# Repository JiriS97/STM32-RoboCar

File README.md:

# STM32-RoboCar
All of this work is licensed under the MIT License - please see license.txt for details.

STM32 based robotic car

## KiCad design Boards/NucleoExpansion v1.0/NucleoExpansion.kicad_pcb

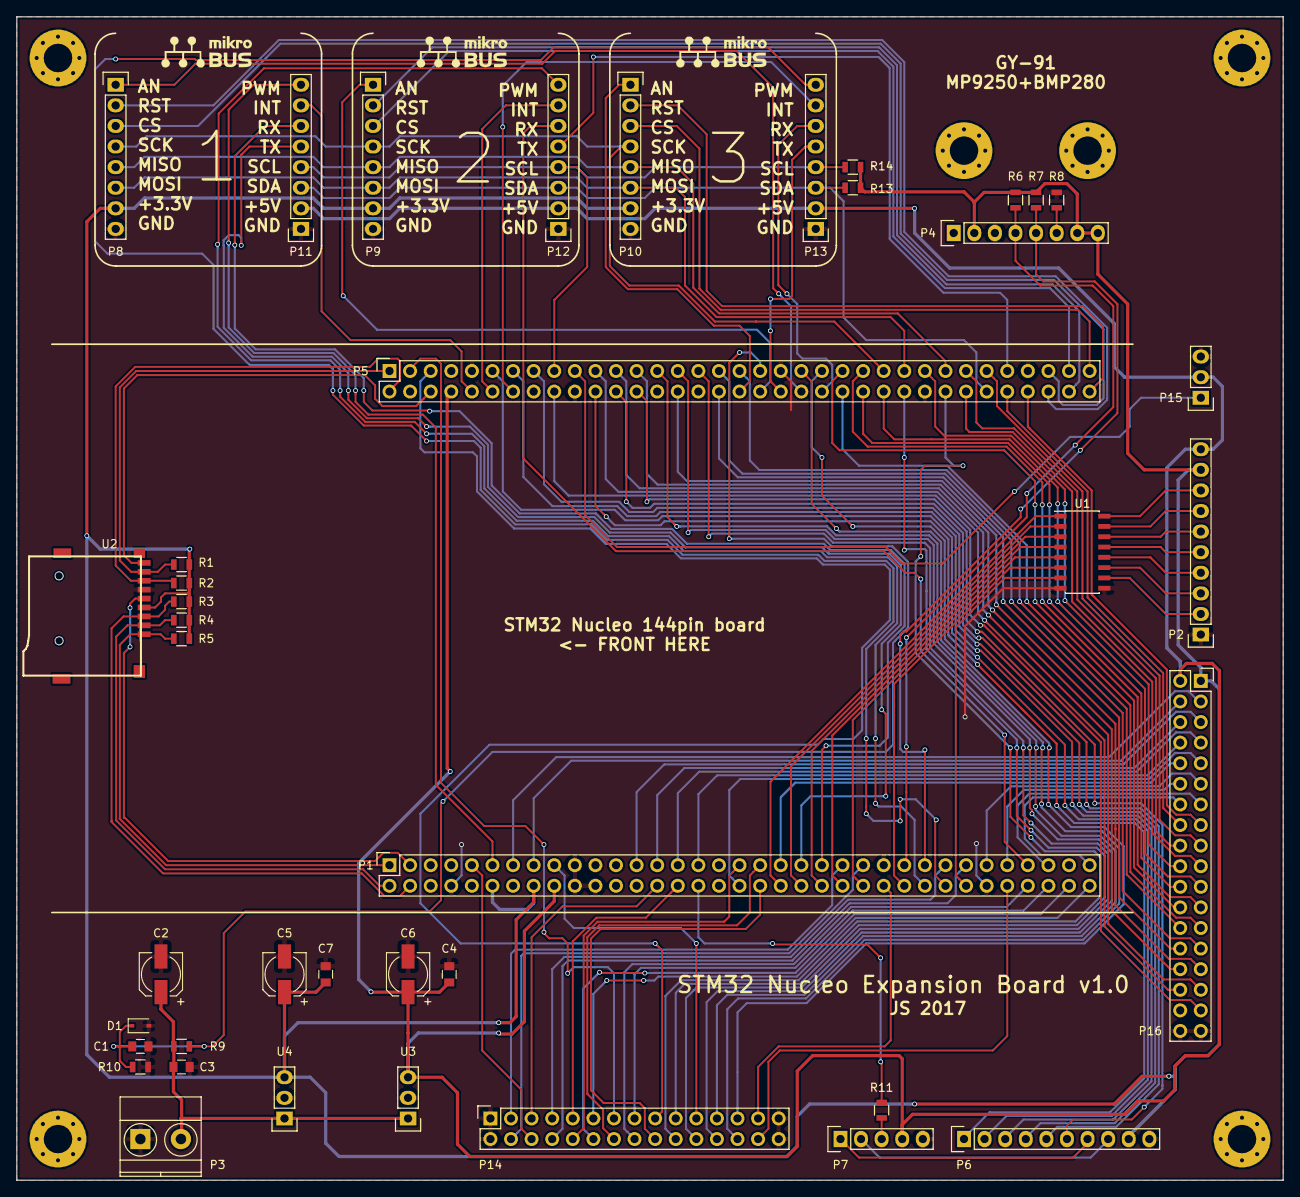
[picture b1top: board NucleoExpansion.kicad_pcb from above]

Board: 2 copper layers, 156.2 x 143.5 mm, 41 parts (0 on the bottom side), 123 nets.

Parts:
C1, C3, C6, C7: 100n; C_0805
C2, C4, C5: 10u; CP_Elec_5x5.7
D1: 3V3; D_SOD-323
P1, P5: CONN_02X35; Socket_Strip_Straight_2x35
P2: TRANSISTOR_OUT; Socket_Strip_Straight_1x10
P3: POWER_IN; TerminalBlock_Pheonix_MKDS1.5-2pol
P4: 10-DOF; Socket_Strip_Straight_1x08
P6: LCD; Socket_Strip_Straight_1x10
P7: AUDIO/ANALOG; Socket_Strip_Straight_1x05
P8: MIKROBUS1.L; Socket_Strip_Straight_1x08
P9: MIKROBUS2.L; Socket_Strip_Straight_1x08
P10: MIKROBUS3.L; Socket_Strip_Straight_1x08
P11: MIKROBUS1.R; Socket_Strip_Straight_1x08
P12: MIKROBUS2.R; Socket_Strip_Straight_1x08
P13: MIKROBUS3.R; Socket_Strip_Straight_1x08
P14: MOTOR; Socket_Strip_Straight_2x15
P15: LED; Socket_Strip_Straight_1x03
P16: FREE_PINS; Socket_Strip_Straight_2x18
R1, R2: 47K; R_0805
R3, R4, R5: 47k; R_0805
R6, R7, R13, R14: 4k7; R_0805
R8: 100R; R_0805
R9: 9k1; R_0805
R10: 1k; R_0805
R11: 10R; R_0805
U1: ULN2003; SOIC-16_3.9x9.9mm_Pitch1.27mm
U2: MicroSD_SPI_CD; microsd
U3: K7805; Socket_Strip_Straight_1x03
U4: K7803; Socket_Strip_Straight_1x03

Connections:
+3V3: C5.1, C7.1, P1.12, P1.16, P2.9, P4.2, P4.7, P4.8, P6.9, P8.7, P9.7, P10.7, P16.1, R1.1, R2.1, R3.1, R4.1, R5.1, R6.1, R7.1, R13.1, R14.1, U2.4, U4.3
+5V: C4.1, C6.1, P1.18, P2.10, P5.8, P7.4, P11.2, P12.2, P13.2, P15.2, P16.2, U3.3
/FREE1: P1.13, P16.3
/FREE2: P1.15, P16.4
/FREE3: P1.25, P16.5
/FREE4: P1.27, P16.6
/FREE5: P1.29, P16.7
/FREE6: P1.31, P16.8
/FREE7: P1.36, P16.9
/FREE8: P1.39, P16.10
/FREE9: P1.59, P16.11
/FREE10: P1.61, P16.12
/FREE11: P1.65, P16.13
/FREE12: P1.69, P16.14
/FREE13: P5.64, P16.15
/FREE14: P5.62, P16.16
/FREE15: P5.59, P16.17
/FREE16: P5.57, P16.18
/FREE17: P5.58, P16.19
/FREE18: P5.53, P16.20
/FREE19: P5.50, P16.21
/FREE20: P5.48, P16.22
/FREE21: P5.47, P16.23
/FREE22: P5.45, P16.24
/FREE23: P5.46, P16.25
/FREE24: P5.35, P16.26
/FREE25: P5.33, P16.27
/FREE26: P5.34, P16.28
/FREE27: P5.30, P16.29
/FREE28: P5.25, P16.30
/FREE29: P5.23, P16.31
/FREE30: P5.21, P16.32
/FREE31: P5.18, P16.33
/LCD.AUDIO+: P6.7, P7.1
/LCD.AUDIO-: P6.8, P7.2
/PA0/PWM5.1/MOTOR1.EN: P1.28, P14.5
/PA1/PWM5.2/MOTOR2.EN: P1.30, P14.9
/PA3/AN3/BATTERY_AN: C1.1, D1.1, P5.37, R9.2, R10.1
/PA4/ANALOG_OUT: P1.32, R11.2
/PA5/SPI1.SCK/LCD.SCK: P5.11, P6.2
/PA6/SPI1.MISO/LCD.MISO: P5.13, P6.3
/PA7/SPI.MOSI/LCD.MOSI: P5.15, P6.4
/PA11/CLICK3.INT: P5.14, P13.7
/PA12/CLICK2.INT: P5.12, P12.7
/PA15/PWM2.1/ENC2.1: P1.17, P14.21
/PB1/LCD.INT: P5.24, P6.5
/PB2/LCD.CS: P5.22, P6.1
/PB3/PWM2.2/ENC2.2: P5.31, P14.22
/PB4/PWM3.1/ENC3.1: P5.27, P14.23
/PB5/PWM3.2/ENC3.2: P5.29, P14.24
/PB6/I2C4.SCL/CLICK.SCL: P5.17, P11.4, P12.4, P13.4, R14.2
/PB8/PWM10.1/MOTOR3.EN: P5.3, P14.13
/PB9/PWM11.1/MOTOR4.EN: P5.5, P14.17
/PB15/LCD.PD: P5.26, P6.6
/PC0/ADC123.IN10/MOTOR4.AN: P1.38, P14.18
/PC2/ADC123.IN12/MOTOR2.AN: P1.35, P14.10
/PC3/ADC123.IN13/MOTOR3.AN: P1.37, P14.14
/PC5/SDMMC.DETECT: P5.6, U2.9
/PC7/PWM8.2/NEOPIXEL: P5.19, P15.1
/PC8/SDMMC.D0: P5.2, R2.2, U2.7
/PC9/SDMMC.D1: P5.1, R1.2, U2.8
/PC10/SDMMC.D2: P1.1, R5.2, U2.1
/PC11/SDMMC.D3: P1.2, R4.2, U2.2
/PC12/SDMMC.CK: P1.3, U2.5
/PD0/MOTOR2.B: P1.57, P14.8
/PD1/MOTOR2.A: P1.55, P14.7
/PD2/SDMMC.CMD: P1.4, R3.2, U2.3
/PD3/TRANSISTOR.1: P1.40, U1.1
/PD5/USART2.TX/CLICK1.TX: P1.41, P11.5
/PD6/USART2.RX/CLICK1.RX: P1.43, P11.6
/PD7/MOTOR1.A: P1.45, P14.3
/PD8/CLICK1.INT: P5.10, P11.7
/PD10/CLICK1.CS: P5.65, P8.3
/PD12/PWM4.1/ENC4.1: P5.43, P14.25
/PD13/PWM4.2/ENC4.2: P5.41, P14.26
/PE2/TRANSISTOR.4: P1.46, U1.4
/PE3/MOTOR1.B: P1.47, P14.4
/PE4/TRANSISTOR.5: P1.48, U1.5
/PE5/PWM9.1/SERVO1: P1.50, P14.27
/PE6/PWM9.2/SERVO2: P1.62, P14.28
/PE7/USART7.RX/CLICK3.RX: P5.44, P13.6
/PE8/USART7.TX/CLICK3.TX: P5.40, P13.5
/PE9/PWM1.1/ENC1.1: P5.52, P14.19
/PE11/PWM1.2/ENC1.2: P5.56, P14.20
/PE12/SPI4.SCK: P5.49, P8.4, P9.4, P10.4
/PE13/SPI4.MISO: P5.55, P8.5, P9.5, P10.5
/PE14/SPI4.MOSI: P5.51, P8.6, P9.6, P10.6
/PF0/I2C2.SDA: P1.53, P4.5, R7.2
/PF1/I2C2.SCL: P1.51, P4.4, R6.2
/PF2/TRANSISTOR.6: P1.52, U1.6
/PF4/ADC3.IN14/CLICK2.AN: P5.38, P9.1
/PF5/ADC3.IN15/CLICK3.AN: P5.36, P10.1
/PF6/ADC3.IN4/MOTOR1.AN: P1.9, P14.6
/PF7/PWM11.1/CLICK1.PWM: P1.11, P11.8
/PF8/PWM13.1/CLICK2.PWM: P1.54, P12.8
/PF9/PWM14.1/CLICK3.PWM: P1.56, P13.8
/PF10/ADC3.IN8/CLICK1.AN: P5.42, P8.1
/PF15/I2C4.SDA/CLICK.SDA: P5.60, P11.3, P12.3, P13.3, R13.2
/PG1/TRANSISTOR.7: P1.58, U1.7
/PG2/TRANSISTOR.2: P1.42, U1.2
/PG3/TRANSISTOR.3: P1.44, U1.3
/PG4/CLICK3.CS: P5.69, P10.3
/PG5/CLICK2.RST: P5.68, P9.2
/PG6/CLICK3.RST: P5.70, P10.2
/PG7/CLICK2.CS: P5.67, P9.3
/PG8/CLICK1.RST: P5.66, P8.2
/PG9/USART6.RX/CLICK2.RX: P1.63, P12.6
/PG10/MOTOR4.A: P1.66, P14.15
/PG11/MOTOR3.A: P1.70, P14.11
/PG13/MOTOR3.B: P1.68, P14.12
/PG14/USART6.TX/CLICK2.TX: P5.61, P12.5
/PG15/MOTOR4.B: P1.64, P14.16
GND: C1.2, C2.2, C3.2, C4.2, C5.2, C6.2, C7.2, D1.2, P1.8, P1.19, P1.20, P1.22, P1.49, P1.60, P2.1, P3.1, P4.3, P5.9, P5.20, P5.39, P5.54, P5.63, P6.10, P7.5, P8.8, P9.8, P10.8, P11.1, P12.1, P13.1, P14.1, P14.2, P14.29, P14.30, P15.3, P16.35, P16.36, R8.2, R10.2, U1.8, U1.9, U2.6, U3.2, U4.2
unnamed: C2.1, C3.1, P3.2, R9.1, U3.1, U4.1
unnamed: P2.2, U1.10
unnamed: P2.3, U1.11
unnamed: P2.4, U1.12
unnamed: P2.5, U1.13
unnamed: P2.6, U1.14
unnamed: P2.7, U1.15
unnamed: P2.8, U1.16
unnamed: P4.6, R8.1
unnamed: P7.3, R11.1

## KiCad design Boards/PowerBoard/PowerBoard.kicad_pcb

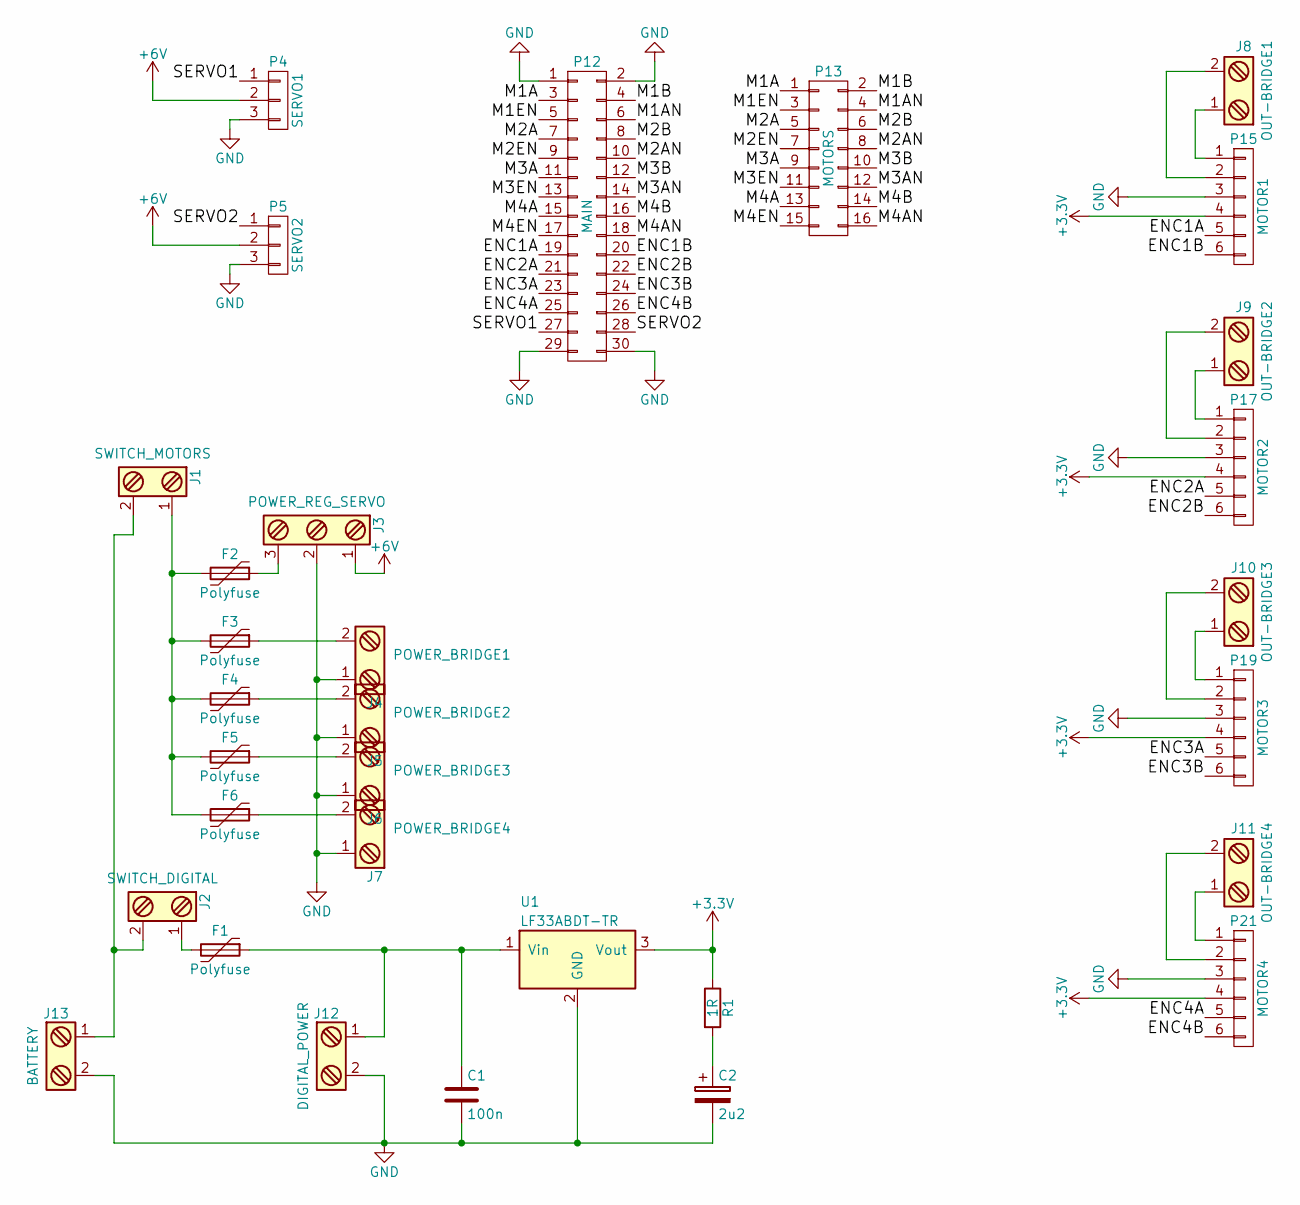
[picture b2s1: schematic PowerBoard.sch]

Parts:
C1: 100n; C_0805
C2: 2u2; CP_Elec_4x4.5
F1, F2, F3, F4, F5, F6: Polyfuse; R_Axial_DIN0204_L3.6mm_D1.6mm_P7.62mm_Horizontal
J1: SWITCH_MOTORS; bornier2
J2: SWITCH_DIGITAL; bornier2
J3: POWER_REG_SERVO; bornier3
J4: POWER_BRIDGE1; bornier2
J5: POWER_BRIDGE2; bornier2
J6: POWER_BRIDGE3; bornier2
J7: POWER_BRIDGE4; bornier2
J8: OUT-BRIDGE1; bornier2
J9: OUT-BRIDGE2; bornier2
J10: OUT-BRIDGE3; bornier2
J11: OUT-BRIDGE4; bornier2
J12: DIGITAL_POWER; bornier2
J13: BATTERY; bornier2
P4: SERVO1; Pin_Header_Straight_1x03_Pitch2.54mm
P5: SERVO2; Pin_Header_Straight_1x03_Pitch2.54mm
P12: MAIN; Pin_Header_Straight_2x15_Pitch2.54mm
P13: MOTORS; Pin_Header_Straight_2x08_Pitch2.54mm
P15: MOTOR1; Pin_Header_Straight_1x06_Pitch2.54mm
P17: MOTOR2; Pin_Header_Straight_1x06_Pitch2.54mm
P19: MOTOR3; Pin_Header_Straight_1x06_Pitch2.54mm
P21: MOTOR4; Pin_Header_Straight_1x06_Pitch2.54mm
R1: 1R; R_0805
U1: LF33ABDT-TR; TO-252-2Lead

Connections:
+3V3: P15.4, P17.4, P19.4, P21.4, R1.1, U1.3 (Vout)
+6V: J3.1, P4.2, P5.2
/ENC1A: P12.19, P15.5
/ENC1B: P12.20, P15.6
/ENC2A: P12.21, P17.5
/ENC2B: P12.22, P17.6
/ENC3A: P12.23, P19.5
/ENC3B: P12.24, P19.6
/ENC4A: P12.25, P21.5
/ENC4B: P12.26, P21.6
/M1A: P12.3, P13.1
/M1AN: P12.6, P13.4
/M1B: P12.4, P13.2
/M1EN: P12.5, P13.3
/M2A: P12.7, P13.5
/M2AN: P12.10, P13.8
/M2B: P12.8, P13.6
/M2EN: P12.9, P13.7
/M3A: P12.11, P13.9
/M3AN: P12.14, P13.12
/M3B: P12.12, P13.10
/M3EN: P12.13, P13.11
/M4A: P12.15, P13.13
/M4AN: P12.18, P13.16
/M4B: P12.16, P13.14
/M4EN: P12.17, P13.15
/SERVO1: P4.1, P12.27
/SERVO2: P5.1, P12.28
GND: C1.2, C2.2, J3.2, J4.1, J5.1, J6.1, J7.1, J12.2, J13.2, P4.3, P5.3, P12.1, P12.2, P12.29, P12.30, P15.3, P17.3, P19.3, P21.3, U1.2 (GND)
unnamed: C1.1, F1.1, J12.1, U1.1 (Vin)
unnamed: C2.1, R1.2
unnamed: F1.2, J2.1
unnamed: F2.1, J3.3
unnamed: F2.2, F3.2, F4.2, F5.2, F6.2, J1.1
unnamed: F3.1, J4.2
unnamed: F4.1, J5.2
unnamed: F5.1, J6.2
unnamed: F6.1, J7.2
unnamed: J1.2, J2.2, J13.1
unnamed: J8.1, P15.1
unnamed: J8.2, P15.2
unnamed: J9.1, P17.1
unnamed: J9.2, P17.2
unnamed: J10.1, P19.1
unnamed: J10.2, P19.2
unnamed: J11.1, P21.1
unnamed: J11.2, P21.2

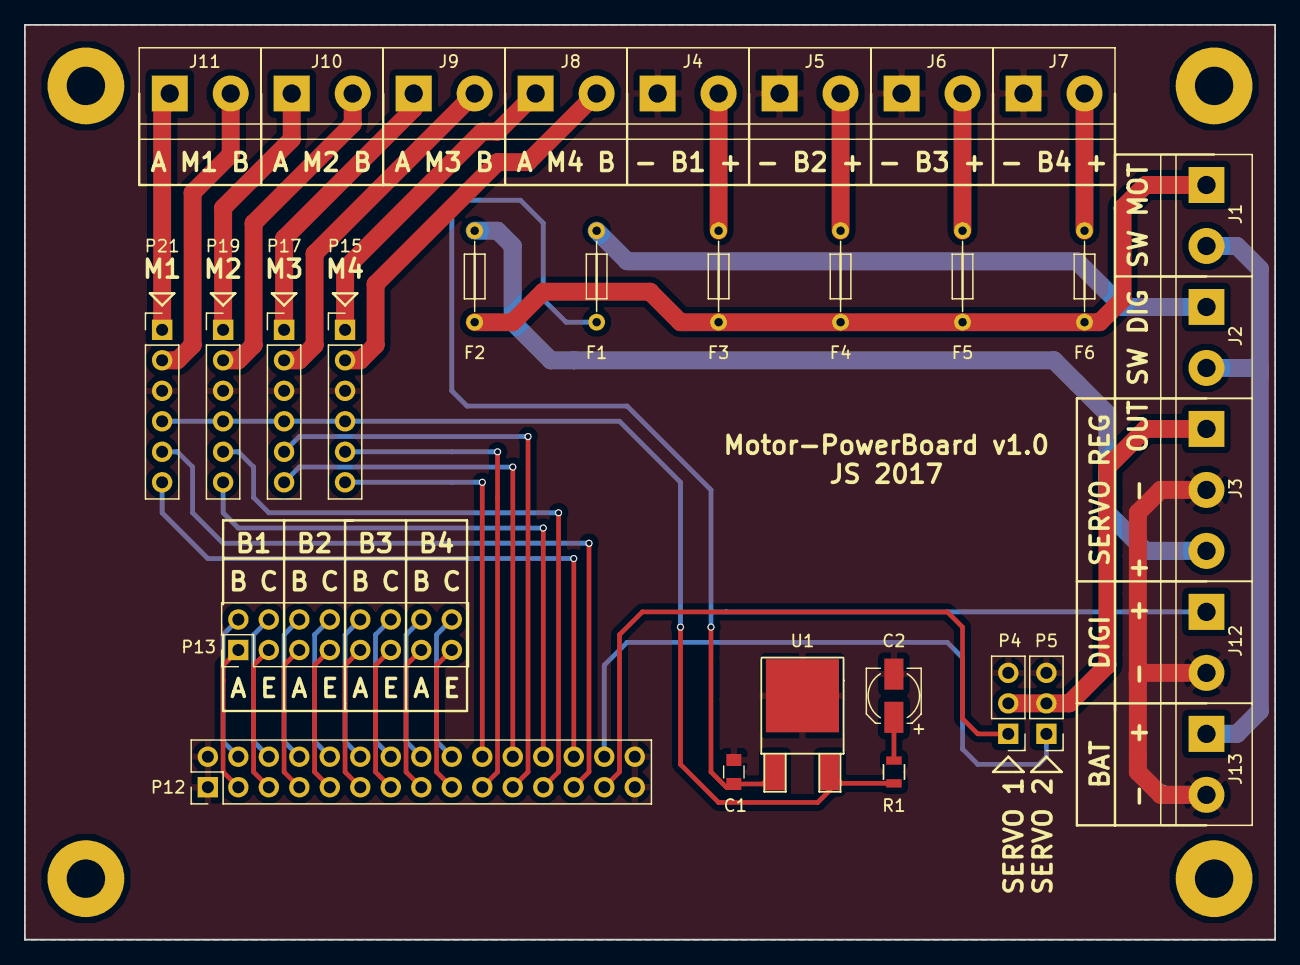
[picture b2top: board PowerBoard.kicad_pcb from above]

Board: 2 copper layers, 104.1 x 76.2 mm, 31 parts (0 on the bottom side), 47 nets.

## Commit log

2017-01-27 :tada: Added .gitattributes
2017-01-27 Added chassis with suspension
    Added drawings of chassis with suspension made in SolidWorks
2017-01-27 Added simple chassis
    Added drawings of simple chassis for prototype made in SolidWorks
2017-01-27 Added MainBoard
    Added MainBoard files and gerbers
2017-02-03 Added PowerBoard
    Added PowerBoard for connecting motors and power supply
2017-02-28 Updated NucleoExpansion to v1.1
    Smaller NucleoExpansion v1.1 board with more optimized layout
2017-02-28 Added license
    Added license, updated README.md
